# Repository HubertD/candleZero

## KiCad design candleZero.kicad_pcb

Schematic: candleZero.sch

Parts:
C1, C2, C3, C4, C5, C6, C8, C10: 100nF; C_0603_1608Metric
C7, C9, C11: 1uF; C_0603_1608Metric
D1: LED_RGB; LED_RGB_PLCC-6
J1: DB9_Male; DSUB-9_Male_EdgeMount_P2.77mm
R1, R2, R3: R; R_0603_1608Metric
R5, R6: 10k; R_0603_1608Metric
TP1: D-; TestPoint_THTPad_1.5x1.5mm_Drill0.7mm
TP2: D+; TestPoint_THTPad_1.5x1.5mm_Drill0.7mm
TP3: +5V; TestPoint_THTPad_1.5x1.5mm_Drill0.7mm
TP4: GND; TestPoint_THTPad_1.5x1.5mm_Drill0.7mm
TP5: VCC; TestPoint_Pad_D1.0mm
TP6: RESET; TestPoint_Pad_D1.0mm
TP7: SWDIO; TestPoint_Pad_D1.0mm
TP8: SWCLK; TestPoint_Pad_D1.0mm
TP9: GND; TestPoint_Pad_D1.0mm
U1: STM32F072RBHx; UFBGA-64_5x5mm_Layout8x8_P0.5mm
U2: TJA1051T-3; DFN-8_2x2mm_P0.5mm
U3: TLV70233_SOT23-5; SOT-23-5

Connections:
+3V3: C2.1, C3.1, C4.1, C5.1, C6.1, C8.1, C10.1, C11.1, R1.2, R2.2, R3.2, R6.2, TP5.1, U1.A2, U1.B2, U1.D1, U1.D2, U1.E4, U1.E5, U1.E6, U1.F4, U1.F5, U1.F6, U1.H1, U2.5, U3.5
+5V: C7.1, C9.2, TP3.1, U2.3, U3.1, U3.3
B: D1.3 (BK), U1.F8
BOOT0: R5.1, U1.A4, U1.B4
D+: TP2.1, U1.B8
D-: TP1.1, U1.C8
G: D1.2 (GK), U1.E8
GND: C1.2, C2.2, C3.2, C4.2, C5.2, C6.2, C7.2, C8.2, C9.1, C10.2, C11.2, R5.2, TP4.1, TP9.1, U1.C1, U1.C2, U1.C4, U1.C5, U1.C6, U1.D4, U1.D5, U1.D6, U1.F1, U1.F2, U2.2, U3.2
unnamed: D1.4 (BA), R1.1
unnamed: D1.5 (GA), R2.1
unnamed: D1.6 (RA), R3.1
unnamed: J1.2, U2.6
unnamed: J1.7, U2.7
R: D1.1 (RK), U1.D8
RESET: C1.1, TP6.1, U1.E1
RXD: U1.B3, U1.C3, U2.4
SILENT: R6.1, U1.G1, U2.8
SWCLK: TP8.1, U1.A7
SWDIO: TP7.1, U1.A8
TXD: U1.A3, U2.1

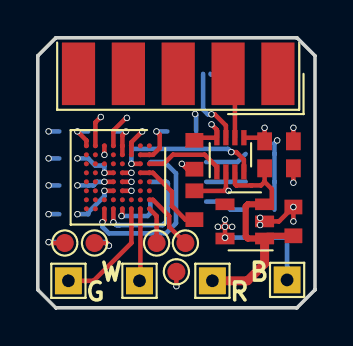
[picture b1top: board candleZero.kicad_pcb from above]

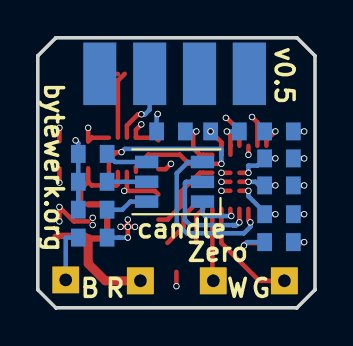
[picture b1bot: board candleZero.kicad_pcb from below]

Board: 4 copper layers, 15.4 x 15.0 mm, 30 parts (12 on the bottom side), 20 nets.

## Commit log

2017-04-28 v0.2
2017-05-14 v0.3
2017-05-14 v0.4
2017-05-17 fix led colors
2018-06-03 v0.5 / bga design test
